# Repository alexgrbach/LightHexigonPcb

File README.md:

# LightHexigonPcb
The pcb that will go into a 3d printed chainable hexigon array

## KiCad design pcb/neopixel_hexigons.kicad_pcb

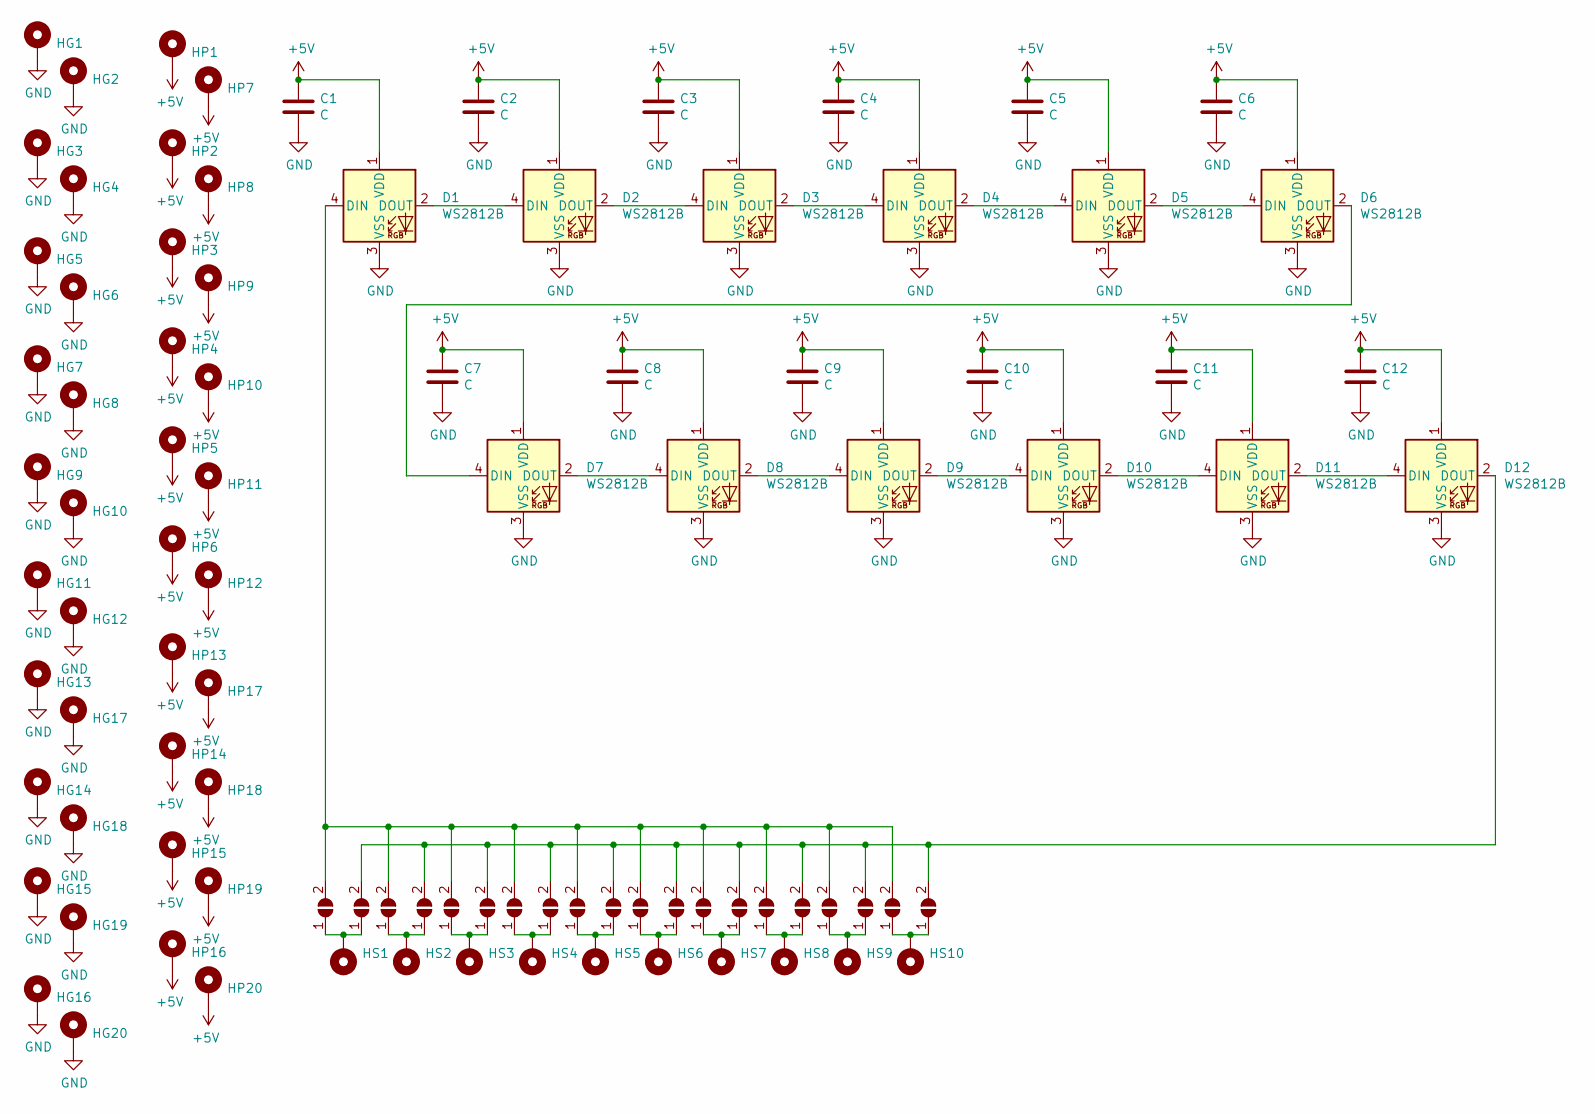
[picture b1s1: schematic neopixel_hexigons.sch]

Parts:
C1, C2, C3, C4, C5, C6, C7, C8, C9, C10, C11, C12: C; C_0603_1608Metric
D1, D2, D3, D4, D5, D6, D7, D8, D9, D10, D11, D12: WS2812B; LED_WS2812B_PLCC4_5.0x5.0mm_P3.2mm
HG1, HG2, HG3, HG4, HG5, HG6, HG7, HG8, HG9, HG10, HG11, HG12, HG13, HG14, HG15, HG16, HG17, HG18, HG19, HG20: MountingHole_Pad; SolderWire-0.1sqmm_1x01_D0.4mm_OD1mm
HP1, HP2, HP3, HP4, HP5, HP6, HP7, HP8, HP9, HP10, HP11, HP12, HP13, HP14, HP15, HP16, HP17, HP18, HP19, HP20: MountingHole_Pad; SolderWire-0.1sqmm_1x01_D0.4mm_OD1mm
HS1, HS2, HS3, HS4, HS5, HS6, HS7, HS8, HS9, HS10: MountingHole_Pad; SolderWire-0.1sqmm_1x01_D0.4mm_OD1mm
JP1, JP2, JP3, JP4, JP5, JP6, JP7, JP8, JP9, JP10, JP11, JP12, JP13, JP14, JP15, JP16, JP17, JP18, JP19, JP20: SolderJumper_2_Open; SolderJumper-2_P1.3mm_Open_Pad1.0x1.5mm

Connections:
+5V: C1.1, C2.1, C3.1, C4.1, C5.1, C6.1, C7.1, C8.1, C9.1, C10.1, C11.1, C12.1, D1.1 (VDD), D2.1 (VDD), D3.1 (VDD), D4.1 (VDD), D5.1 (VDD), D6.1 (VDD), D7.1 (VDD), D8.1 (VDD), D9.1 (VDD), D10.1 (VDD), D11.1 (VDD), D12.1 (VDD), HP1.1, HP2.1, HP3.1, HP4.1, HP5.1, HP6.1, HP7.1, HP8.1, HP9.1, HP10.1, HP11.1, HP12.1, HP13.1, HP14.1, HP15.1, HP16.1, HP17.1, HP18.1, HP19.1, HP20.1
GND: C1.2, C2.2, C3.2, C4.2, C5.2, C6.2, C7.2, C8.2, C9.2, C10.2, C11.2, C12.2, D1.3 (VSS), D2.3 (VSS), D3.3 (VSS), D4.3 (VSS), D5.3 (VSS), D6.3 (VSS), D7.3 (VSS), D8.3 (VSS), D9.3 (VSS), D10.3 (VSS), D11.3 (VSS), D12.3 (VSS), HG1.1, HG2.1, HG3.1, HG4.1, HG5.1, HG6.1, HG7.1, HG8.1, HG9.1, HG10.1, HG11.1, HG12.1, HG13.1, HG14.1, HG15.1, HG16.1, HG17.1, HG18.1, HG19.1, HG20.1
unnamed: D1.2 (DOUT), D2.4 (DIN)
unnamed: D1.4 (DIN), JP1.2 (B), JP3.2 (B), JP5.2 (B), JP7.2 (B), JP9.2 (B), JP11.2 (B), JP13.2 (B), JP15.2 (B), JP17.2 (B), JP19.2 (B)
unnamed: D2.2 (DOUT), D3.4 (DIN)
unnamed: D3.2 (DOUT), D4.4 (DIN)
unnamed: D4.2 (DOUT), D5.4 (DIN)
unnamed: D5.2 (DOUT), D6.4 (DIN)
unnamed: D6.2 (DOUT), D7.4 (DIN)
unnamed: D7.2 (DOUT), D8.4 (DIN)
unnamed: D8.2 (DOUT), D9.4 (DIN)
unnamed: D10.2 (DOUT), D11.4 (DIN)
unnamed: D9.2 (DOUT), D10.4 (DIN)
unnamed: D11.2 (DOUT), D12.4 (DIN)
unnamed: D12.2 (DOUT), JP2.2 (B), JP4.2 (B), JP6.2 (B), JP8.2 (B), JP10.2 (B), JP12.2 (B), JP14.2 (B), JP16.2 (B), JP18.2 (B), JP20.2 (B)
unnamed: HS1.1, JP1.1 (A), JP2.1 (A)
unnamed: HS2.1, JP3.1 (A), JP4.1 (A)
unnamed: HS3.1, JP5.1 (A), JP6.1 (A)
unnamed: HS4.1, JP7.1 (A), JP8.1 (A)
unnamed: HS5.1, JP9.1 (A), JP10.1 (A)
unnamed: HS6.1, JP11.1 (A), JP12.1 (A)
unnamed: HS7.1, JP13.1 (A), JP14.1 (A)
unnamed: HS8.1, JP15.1 (A), JP16.1 (A)
unnamed: HS9.1, JP17.1 (A), JP18.1 (A)
unnamed: HS10.1, JP19.1 (A), JP20.1 (A)

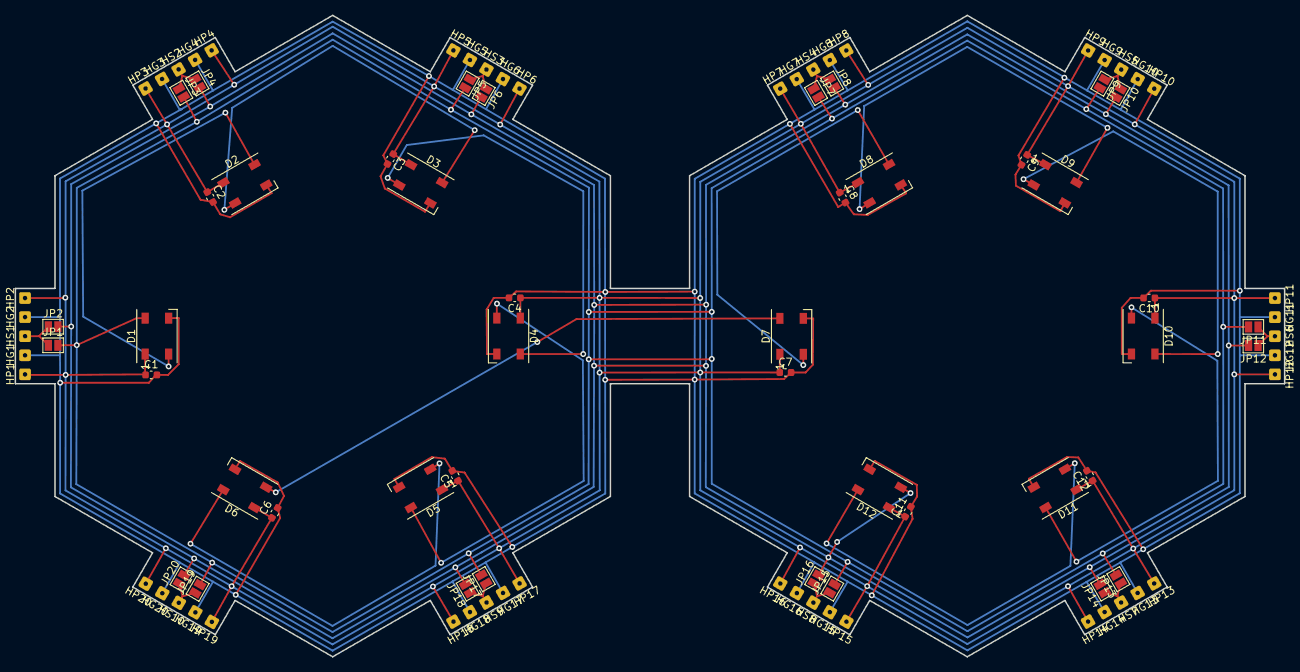
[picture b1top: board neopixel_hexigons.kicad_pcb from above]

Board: 2 copper layers, 173.2 x 87.5 mm, 94 parts (0 on the bottom side), 25 nets.

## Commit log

2021-06-30 Inital Commit
